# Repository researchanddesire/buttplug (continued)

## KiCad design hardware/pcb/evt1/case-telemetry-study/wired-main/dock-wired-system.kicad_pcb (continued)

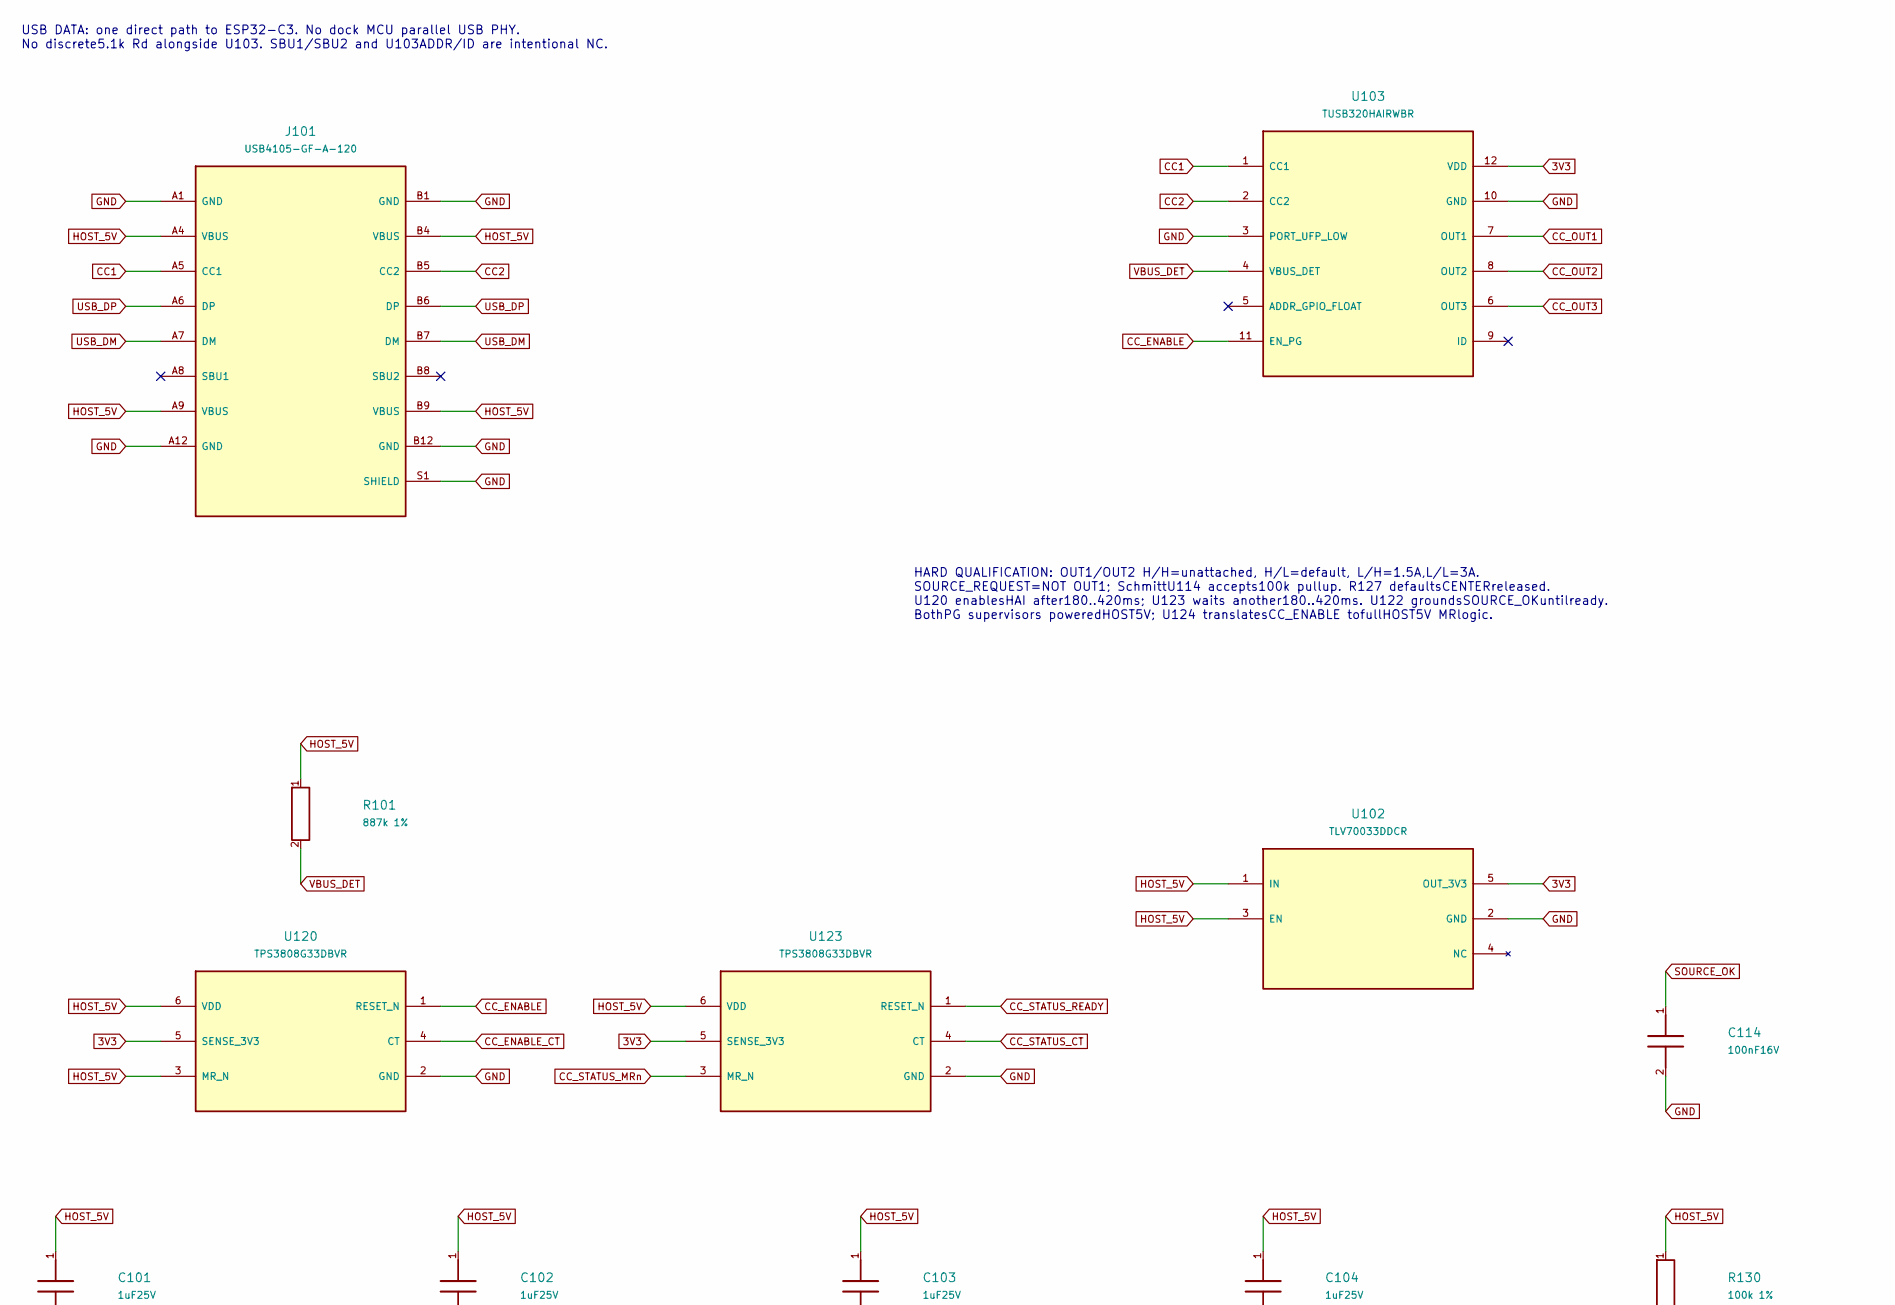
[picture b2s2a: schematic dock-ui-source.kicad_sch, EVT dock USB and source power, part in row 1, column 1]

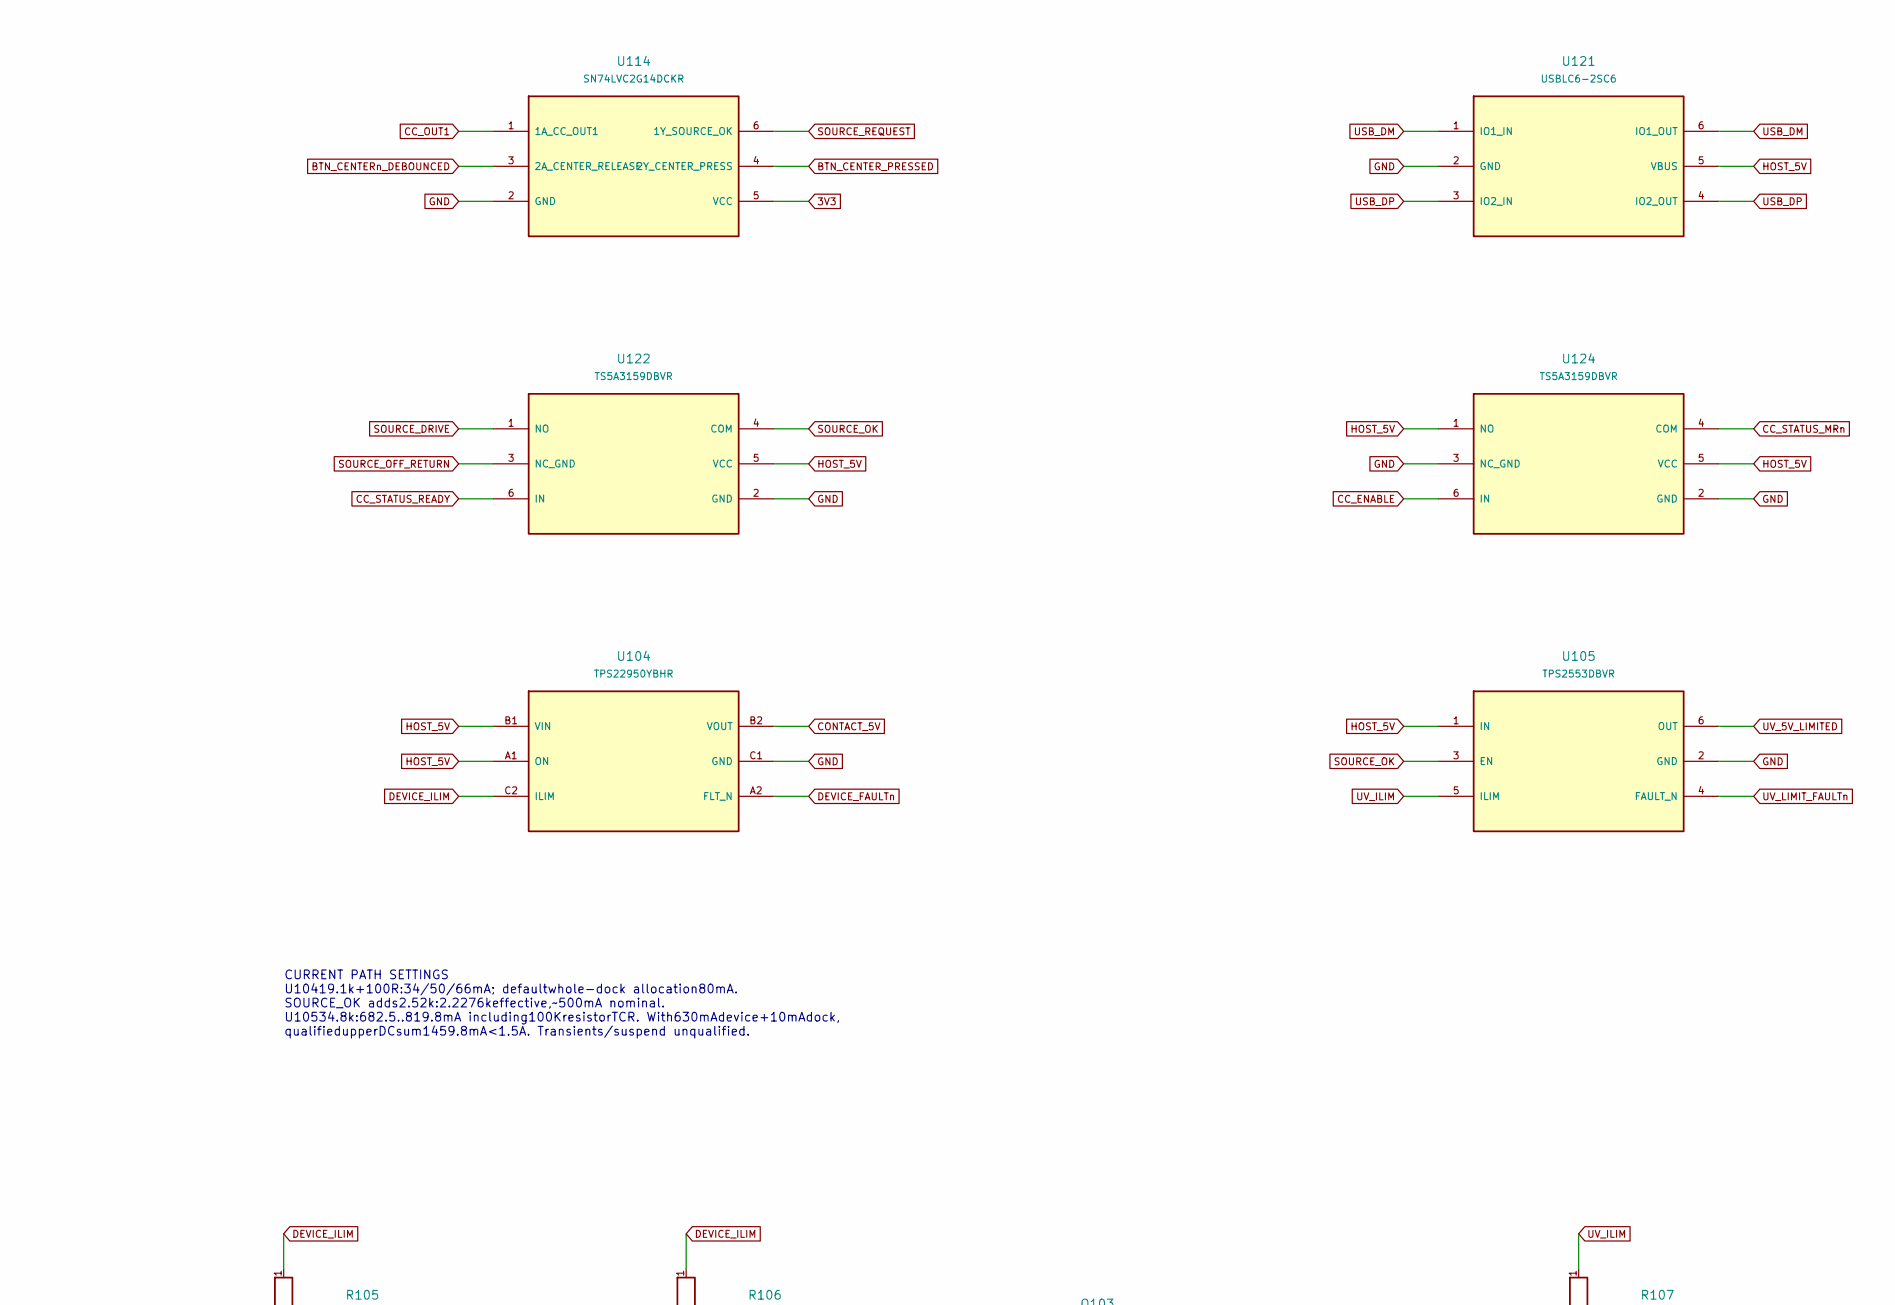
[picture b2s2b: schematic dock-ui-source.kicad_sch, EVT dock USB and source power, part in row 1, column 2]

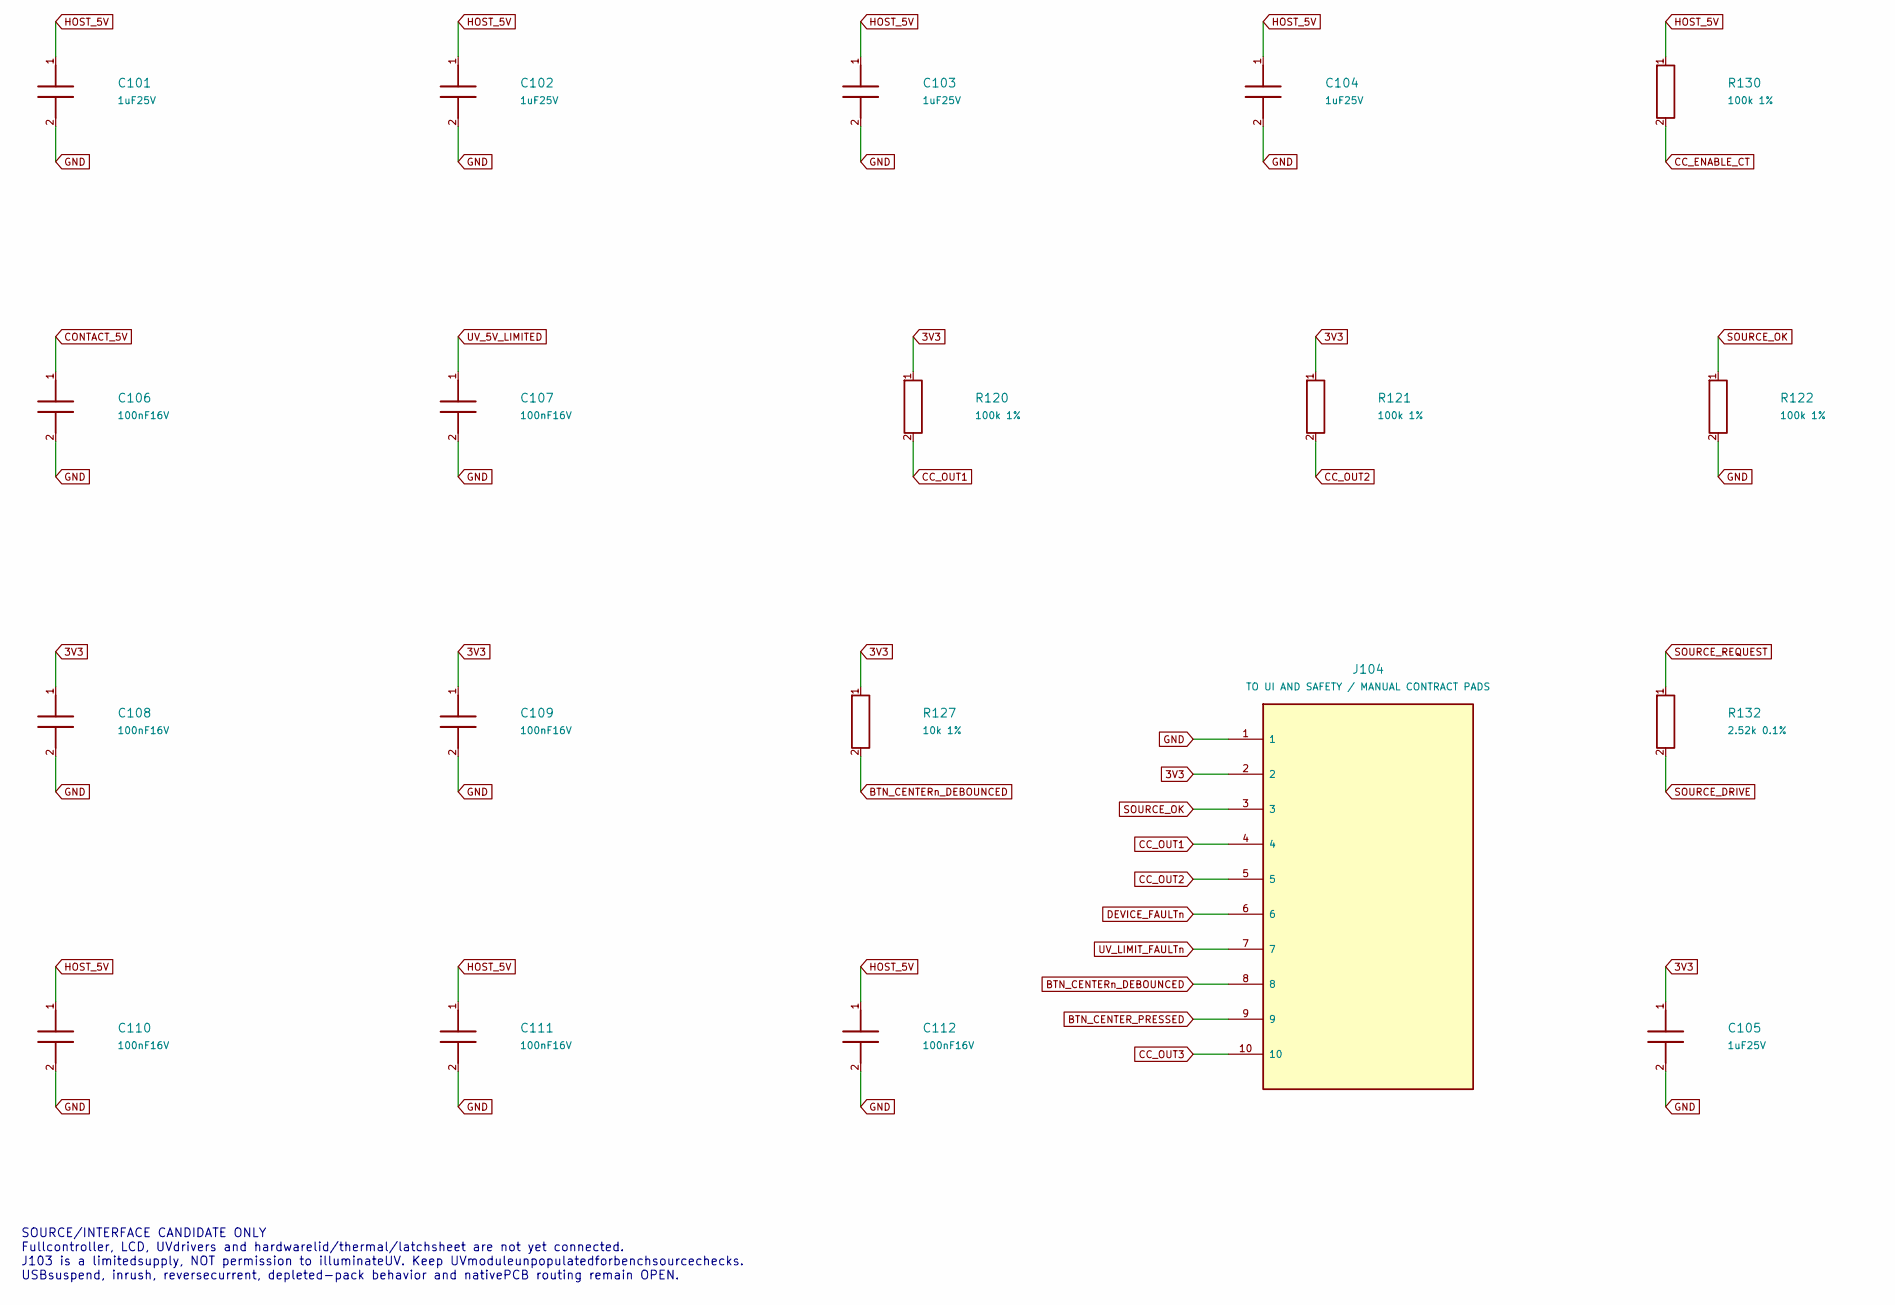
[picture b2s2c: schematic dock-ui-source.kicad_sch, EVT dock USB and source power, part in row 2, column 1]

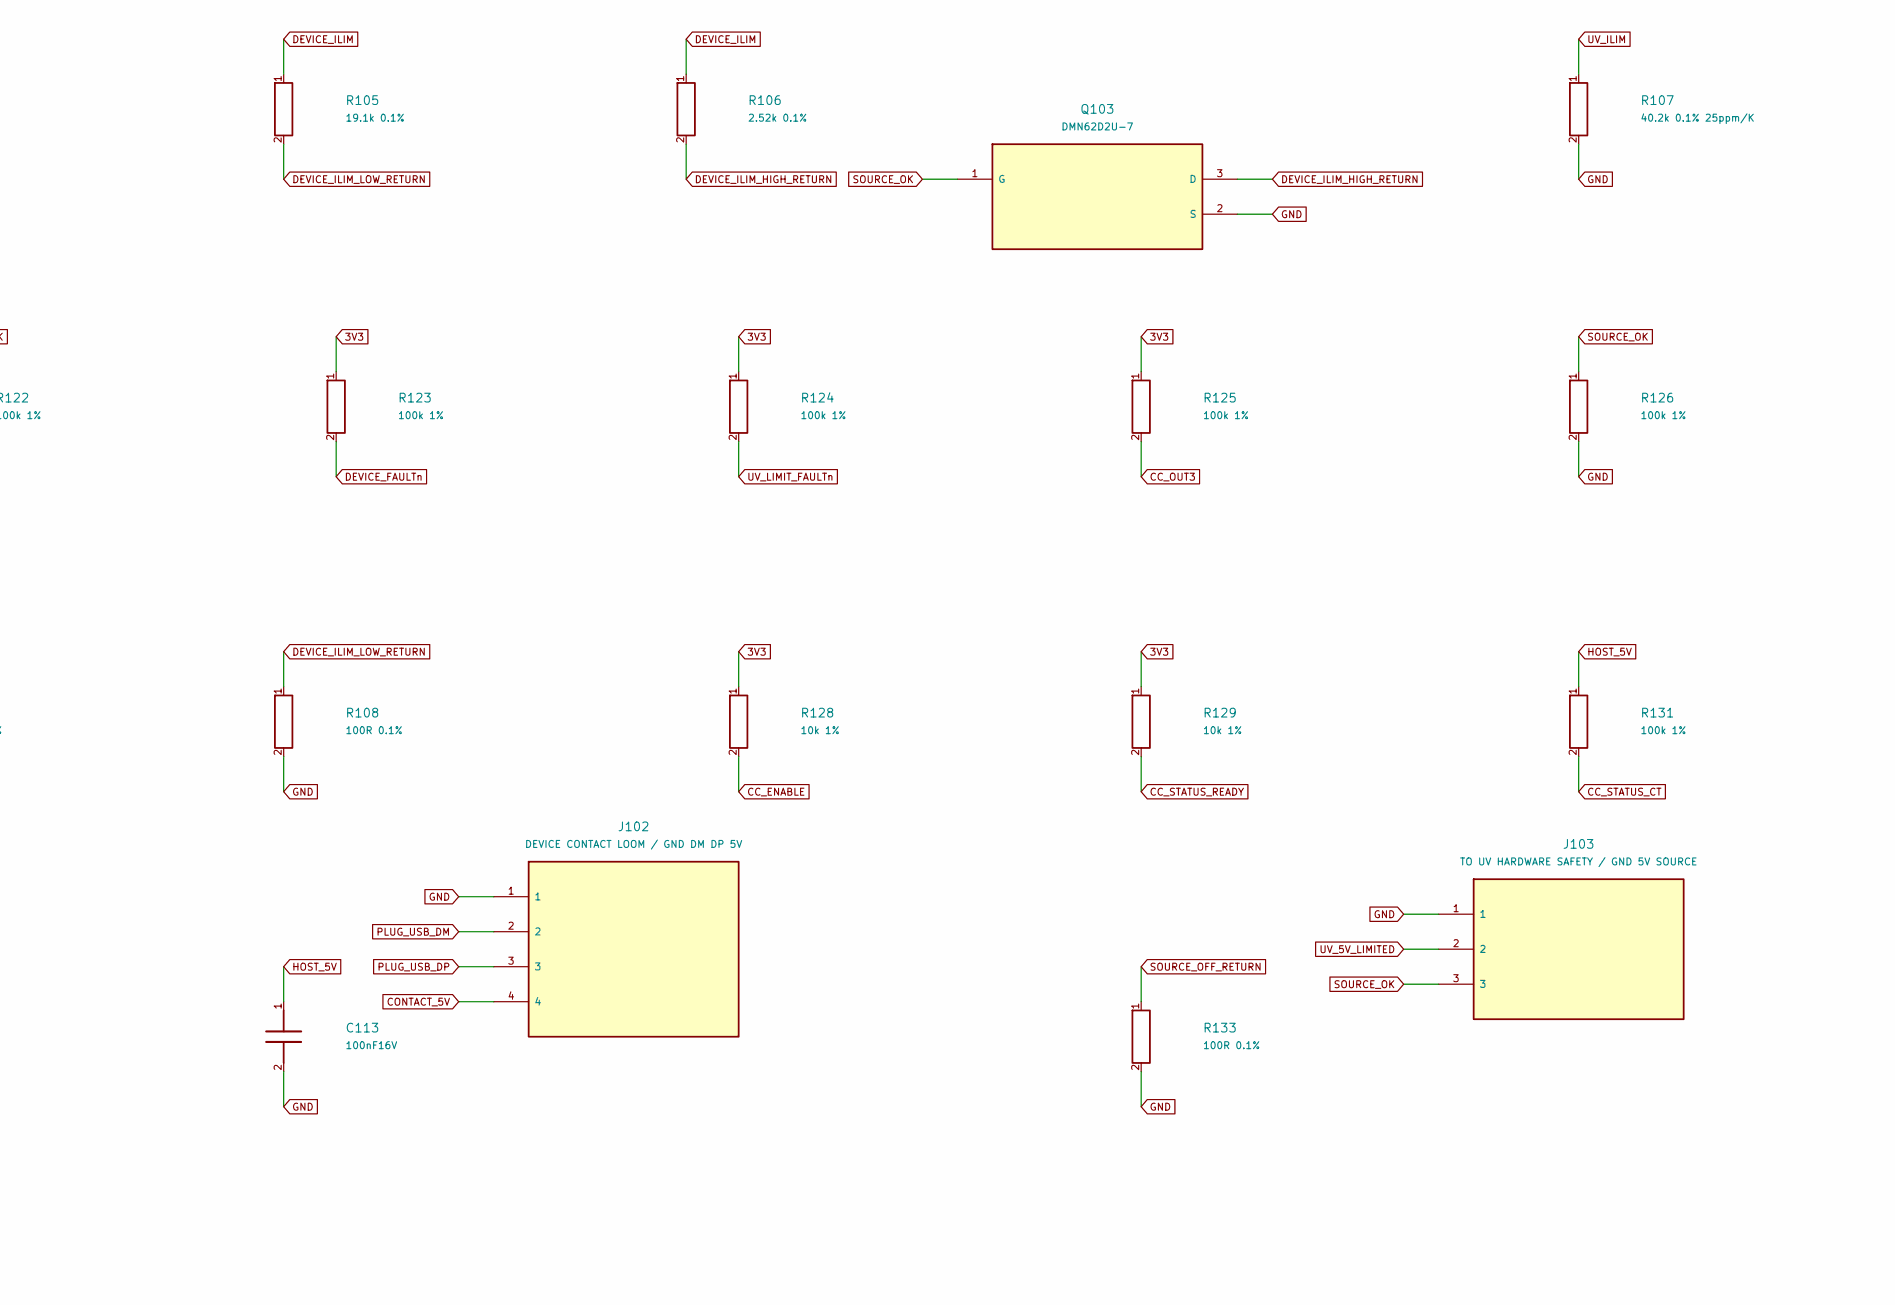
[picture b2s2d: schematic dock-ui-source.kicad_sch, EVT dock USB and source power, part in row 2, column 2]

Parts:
C101, C102, C103, C104, C105: 1uF25V; C_0603_1608Metric; MPN C1608X7R1E105K080AB
C106, C107, C108, C109, C110, C111, C112, C113, C114: 100nF16V; C_0402_1005Metric; MPN GRM155R71C104KA88D
J101: USB4105-GF-A-120; USB_C_Receptacle_GCT_USB4105-xx-A_16P_TopMnt_Horizontal; MPN USB4105-GF-A-120
J102: DEVICE CONTACT LOOM / GND DM DP 5V; Contact_Loom_4Land; MPN DEVICE CONTACT LOOM / GND DM DP 5V
J103: TO UV HARDWARE SAFETY / GND 5V SOURCE; Control_Loom_3Land; MPN TO UV HARDWARE SAFETY / GND 5V SOURCE
J104: TO UI AND SAFETY / MANUAL CONTRACT PADS; Control_Loom_10Land; MPN TO UI AND SAFETY / MANUAL CONTRACT PADS
Q103: DMN62D2U-7; SOT-23; MPN DMN62D2U-7
R101: 887k 1%; R_0603_1608Metric; MPN RC0603FR-07887KL
R105: 19.1k 0.1%; R_0603_1608Metric; MPN RT0603BRD0719K1L
R106, R132: 2.52k 0.1%; R_0603_1608Metric; MPN RT0603BRD072K52L
R107: 40.2k 0.1% 25ppm/K; R_0603_1608Metric; MPN RT0603BRD0740K2L
R108, R133: 100R 0.1%; R_0603_1608Metric; MPN RT0603BRD07100RL
R120, R121, R122, R123, R124, R125, R126, R130, R131: 100k 1%; R_0603_1608Metric; MPN RC0603FR-07100KL
R127, R128, R129: 10k 1%; R_0603_1608Metric; MPN RC0603FR-0710KL
U102: TLV70033DDCR; TSOT-23-5; MPN TLV70033DDCR
U103: TUSB320HAIRWBR; Texas_X2QFN-12_1.6x1.6mm_P0.4mm; MPN TUSB320HAIRWBR
U104: TPS22950YBHR; Texas_YBH0006-C02_DSBGA-6_1.106x0.706mm_P0.4mm; MPN TPS22950YBHR
U105: TPS2553DBVR; SOT-23-6; MPN TPS2553DBVR
U114: SN74LVC2G14DCKR; SOT-363_SC-70-6; MPN SN74LVC2G14DCKR
U120, U123: TPS3808G33DBVR; SOT-23-6; MPN TPS3808G33DBVR
U121: USBLC6-2SC6; SOT-23-6; MPN USBLC6-2SC6
U122, U124: TS5A3159DBVR; SOT-23-6; MPN TS5A3159DBVR

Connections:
3V3: C105.1, C108.1, C109.1, J104.2, R120.1, R121.1, R123.1, R124.1, R125.1, R127.1, R128.1, R129.1, U102.5 (OUT_3V3), U103.12 (VDD), U114.5 (VCC), U120.5 (SENSE_3V3), U123.5 (SENSE_3V3); also elsewhere on the board
BTN_CENTER_PRESSED: J104.9, U114.4 (2Y_CENTER_PRESS); also elsewhere on the board
BTN_CENTERn_DEBOUNCED: J104.8, R127.2, U114.3 (2A_CENTER_RELEASE); also elsewhere on the board
CC1: J101.A5 (CC1), U103.1 (CC1)
CC2: J101.B5 (CC2), U103.2 (CC2)
CC_ENABLE: R128.2, U103.11 (EN_PG), U120.1 (RESET_N), U124.6 (IN); also elsewhere on the board
CC_ENABLE_CT: R130.2, U120.4 (CT)
CC_OUT1: J104.4, R120.2, U103.7 (OUT1), U114.1 (1A_CC_OUT1); also elsewhere on the board
CC_OUT2: J104.5, R121.2, U103.8 (OUT2); also elsewhere on the board
CC_OUT3: J104.10, R125.2, U103.6 (OUT3)
CC_STATUS_CT: R131.2, U123.4 (CT)
CC_STATUS_MRn: U123.3 (MR_N), U124.4 (COM)
CC_STATUS_READY: R129.2, U122.6 (IN), U123.1 (RESET_N)
CONTACT_5V: C106.1, J102.4, U104.B2 (VOUT); also elsewhere on the board
DEVICE_FAULTn: J104.6, R123.2, U104.A2 (FLT_N); also elsewhere on the board
DEVICE_ILIM: R105.1, R106.1, U104.C2 (ILIM)
DEVICE_ILIM_HIGH_RETURN: Q103.3 (D), R106.2
DEVICE_ILIM_LOW_RETURN: R105.2, R108.1
GND: C101.2, C102.2, C103.2, C104.2, C105.2, C106.2, C107.2, C108.2, C109.2, C110.2, C111.2, C112.2, C113.2, C114.2, J101.A1 (GND), J101.A12 (GND), J101.B1 (GND), J101.B12 (GND), J101.S1 (SHIELD), J102.1, J103.1, J104.1, Q103.2 (S), R107.2, R108.2, R122.2, R126.2, R133.2, U102.2 (GND), U103.3 (PORT_UFP_LOW), U103.10 (GND), U104.C1 (GND), U105.2 (GND), U114.2 (GND), U120.2 (GND), U121.2 (GND), U122.2 (GND), U123.2 (GND), U124.2 (GND), U124.3 (NC_GND); also elsewhere on the board
HOST_5V: C101.1, C102.1, C103.1, C104.1, C110.1, C111.1, C112.1, C113.1, J101.A4 (VBUS), J101.A9 (VBUS), J101.B4 (VBUS), J101.B9 (VBUS), R101.1, R130.1, R131.1, U102.1 (IN), U102.3 (EN), U104.A1 (ON), U104.B1 (VIN), U105.1 (IN), U120.3 (MR_N), U120.6 (VDD), U121.5 (VBUS), U122.5 (VCC), U123.6 (VDD), U124.1 (NO), U124.5 (VCC); also elsewhere on the board
PLUG_USB_DM: J102.2; also elsewhere on the board
PLUG_USB_DP: J102.3; also elsewhere on the board
SOURCE_DRIVE: R132.2, U122.1 (NO)
SOURCE_OFF_RETURN: R133.1, U122.3 (NC_GND)
SOURCE_OK: C114.1, J103.3, J104.3, Q103.1 (G), R122.1, R126.1, U105.3 (EN), U122.4 (COM); also elsewhere on the board
SOURCE_REQUEST: R132.1, U114.6 (1Y_SOURCE_OK)
USB_DM: J101.A7 (DM), J101.B7 (DM), U121.1 (IO1_IN), U121.6 (IO1_OUT); also elsewhere on the board
USB_DP: J101.A6 (DP), J101.B6 (DP), U121.3 (IO2_IN), U121.4 (IO2_OUT); also elsewhere on the board
UV_5V_LIMITED: C107.1, J103.2, U105.6 (OUT); also elsewhere on the board
UV_ILIM: R107.1, U105.5 (ILIM)
UV_LIMIT_FAULTn: J104.7, R124.2, U105.4 (FAULT_N); also elsewhere on the board
VBUS_DET: R101.2, U103.4 (VBUS_DET)

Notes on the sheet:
USB DATA: one direct path to ESP32-C3. No dock MCU parallel USB PHY. No discrete5.1k Rd alongside U103. SBU1/SBU2 and U103ADDR/ID are intentional NC.
HARD QUALIFICATION: OUT1/OUT2 H/H=unattached, H/L=default, L/H=1.5A,L/L=3A. SOURCE_REQUEST=NOT OUT1; SchmittU114 accepts100k pullup. R127 defaultsCENTERreleased. U120 enablesHAI after180..420ms; U123 waits another180..420ms. U122 groundsSOURCE_OKuntilready. BothPG supervisors poweredHOST5V; U124 tr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
CURRENT PATH SETTINGS U10419.1k+100R:34/50/66mA; defaultwhole-dock allocation80mA. SOURCE_OK adds2.52k:2.2276keffective,~500mA nominal. U10534.8k:682.5..819.8mA including100KresistorTCR. With630mAdevice+10mAdock, qualifiedupperDCsum1459.8mA<1.5A. Transients/suspend unqualified.
SOURCE/INTERFACE CANDIDATE ONLY Fullcontroller, LCD, UVdrivers and hardwarelid/thermal/latchsheet are not yet connected. J103 is a limitedsupply, NOT permission to illuminateUV. Keep UVmoduleunpopulatedforbenchsourcechecks. USBsuspend, inrush, reversecurrent, depleted-pack behavior and nativePCB ro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

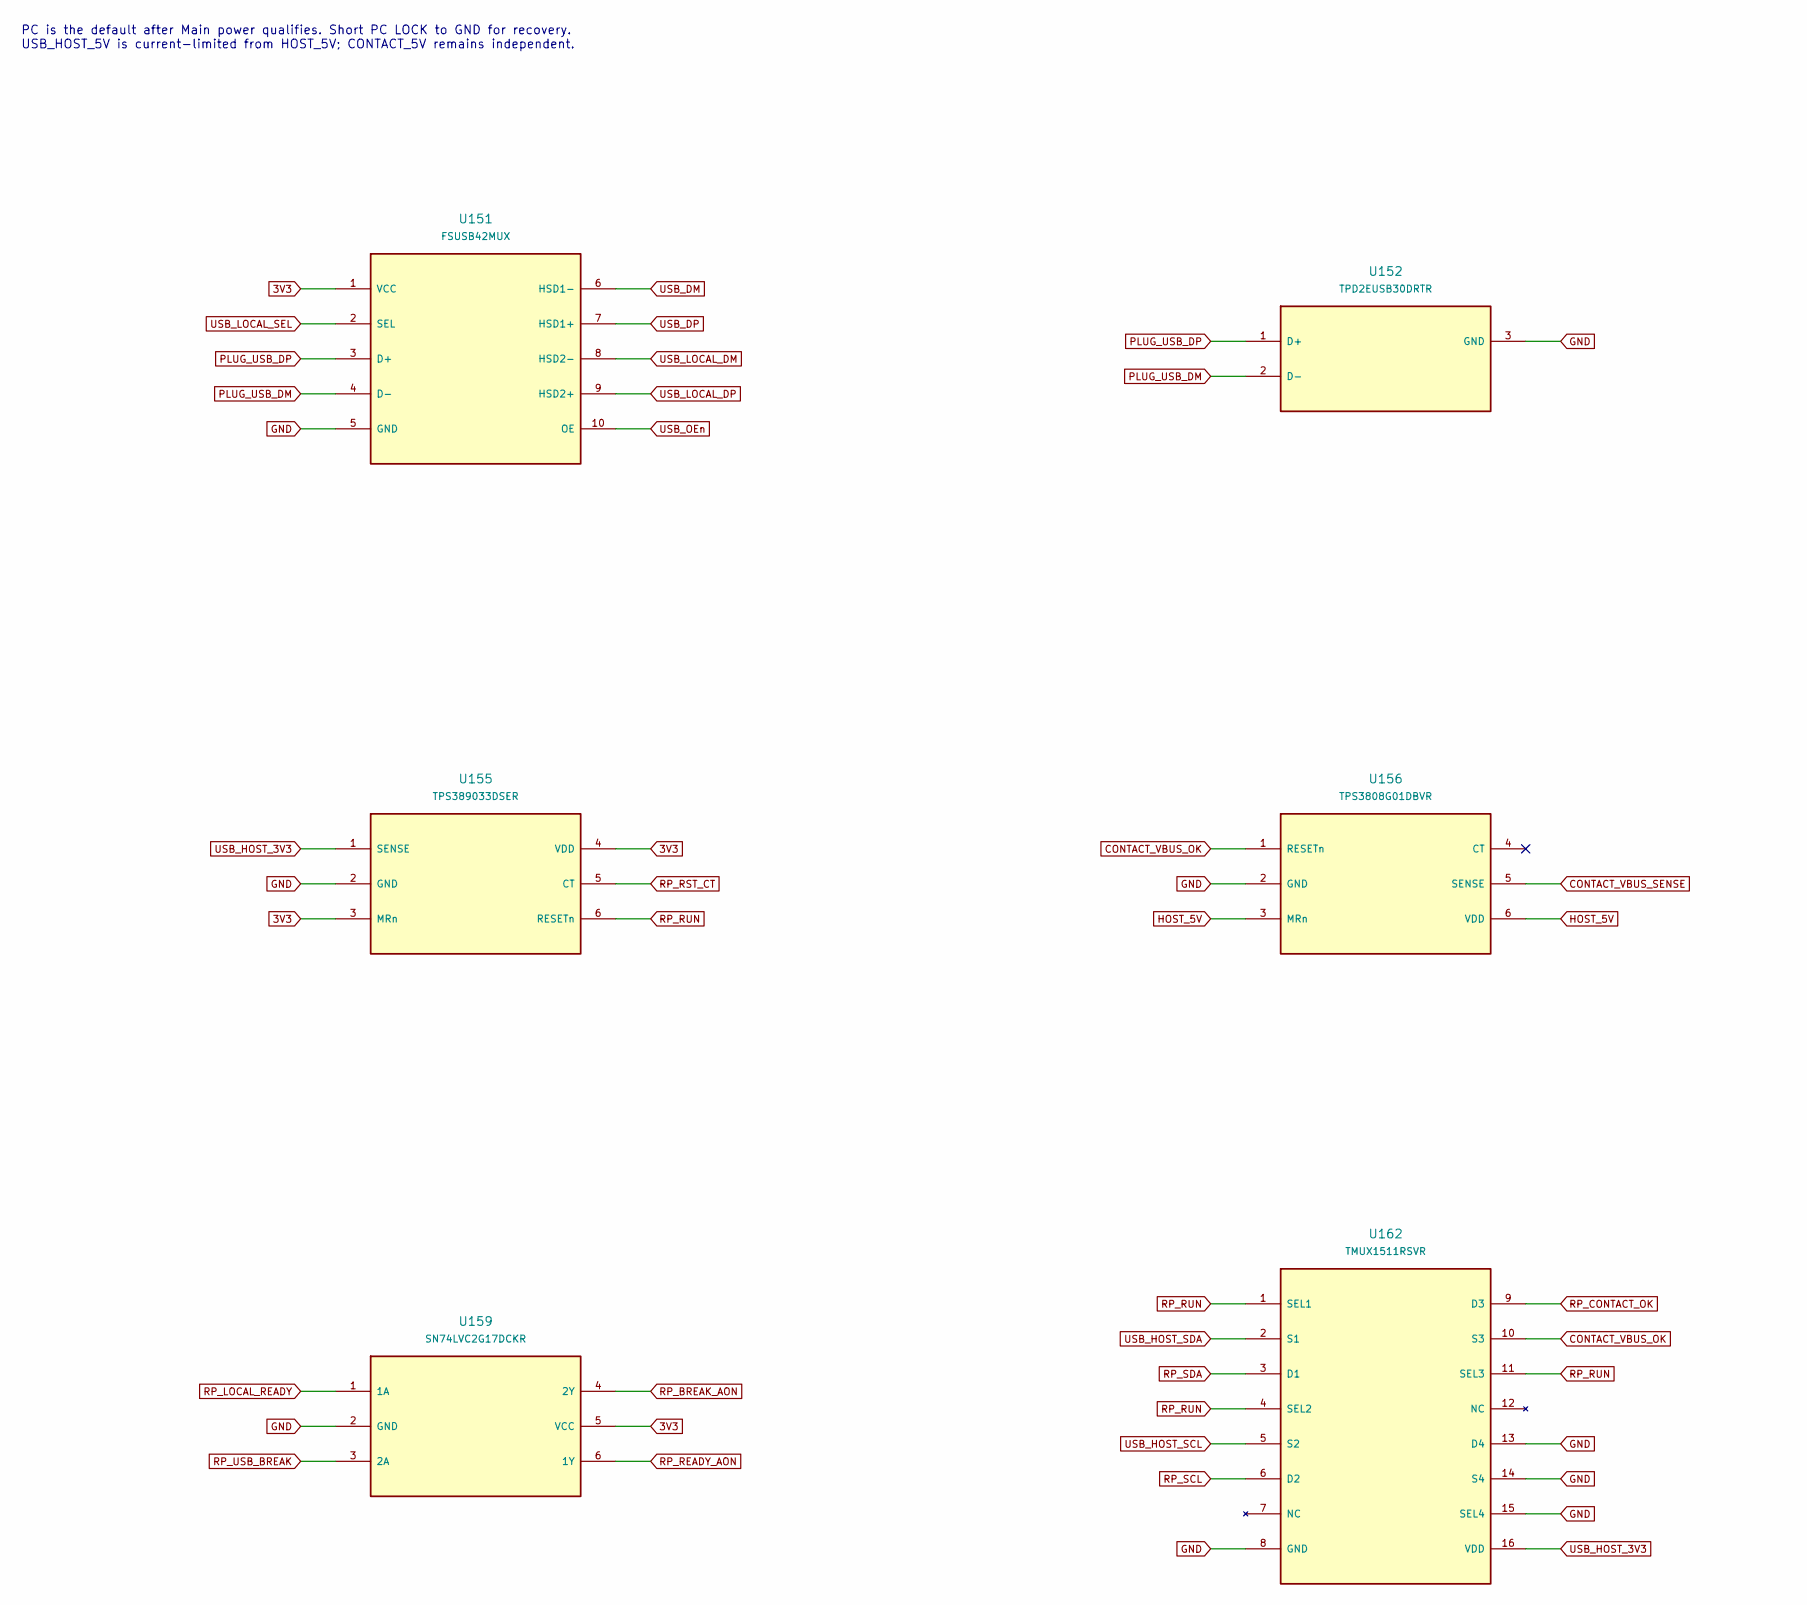
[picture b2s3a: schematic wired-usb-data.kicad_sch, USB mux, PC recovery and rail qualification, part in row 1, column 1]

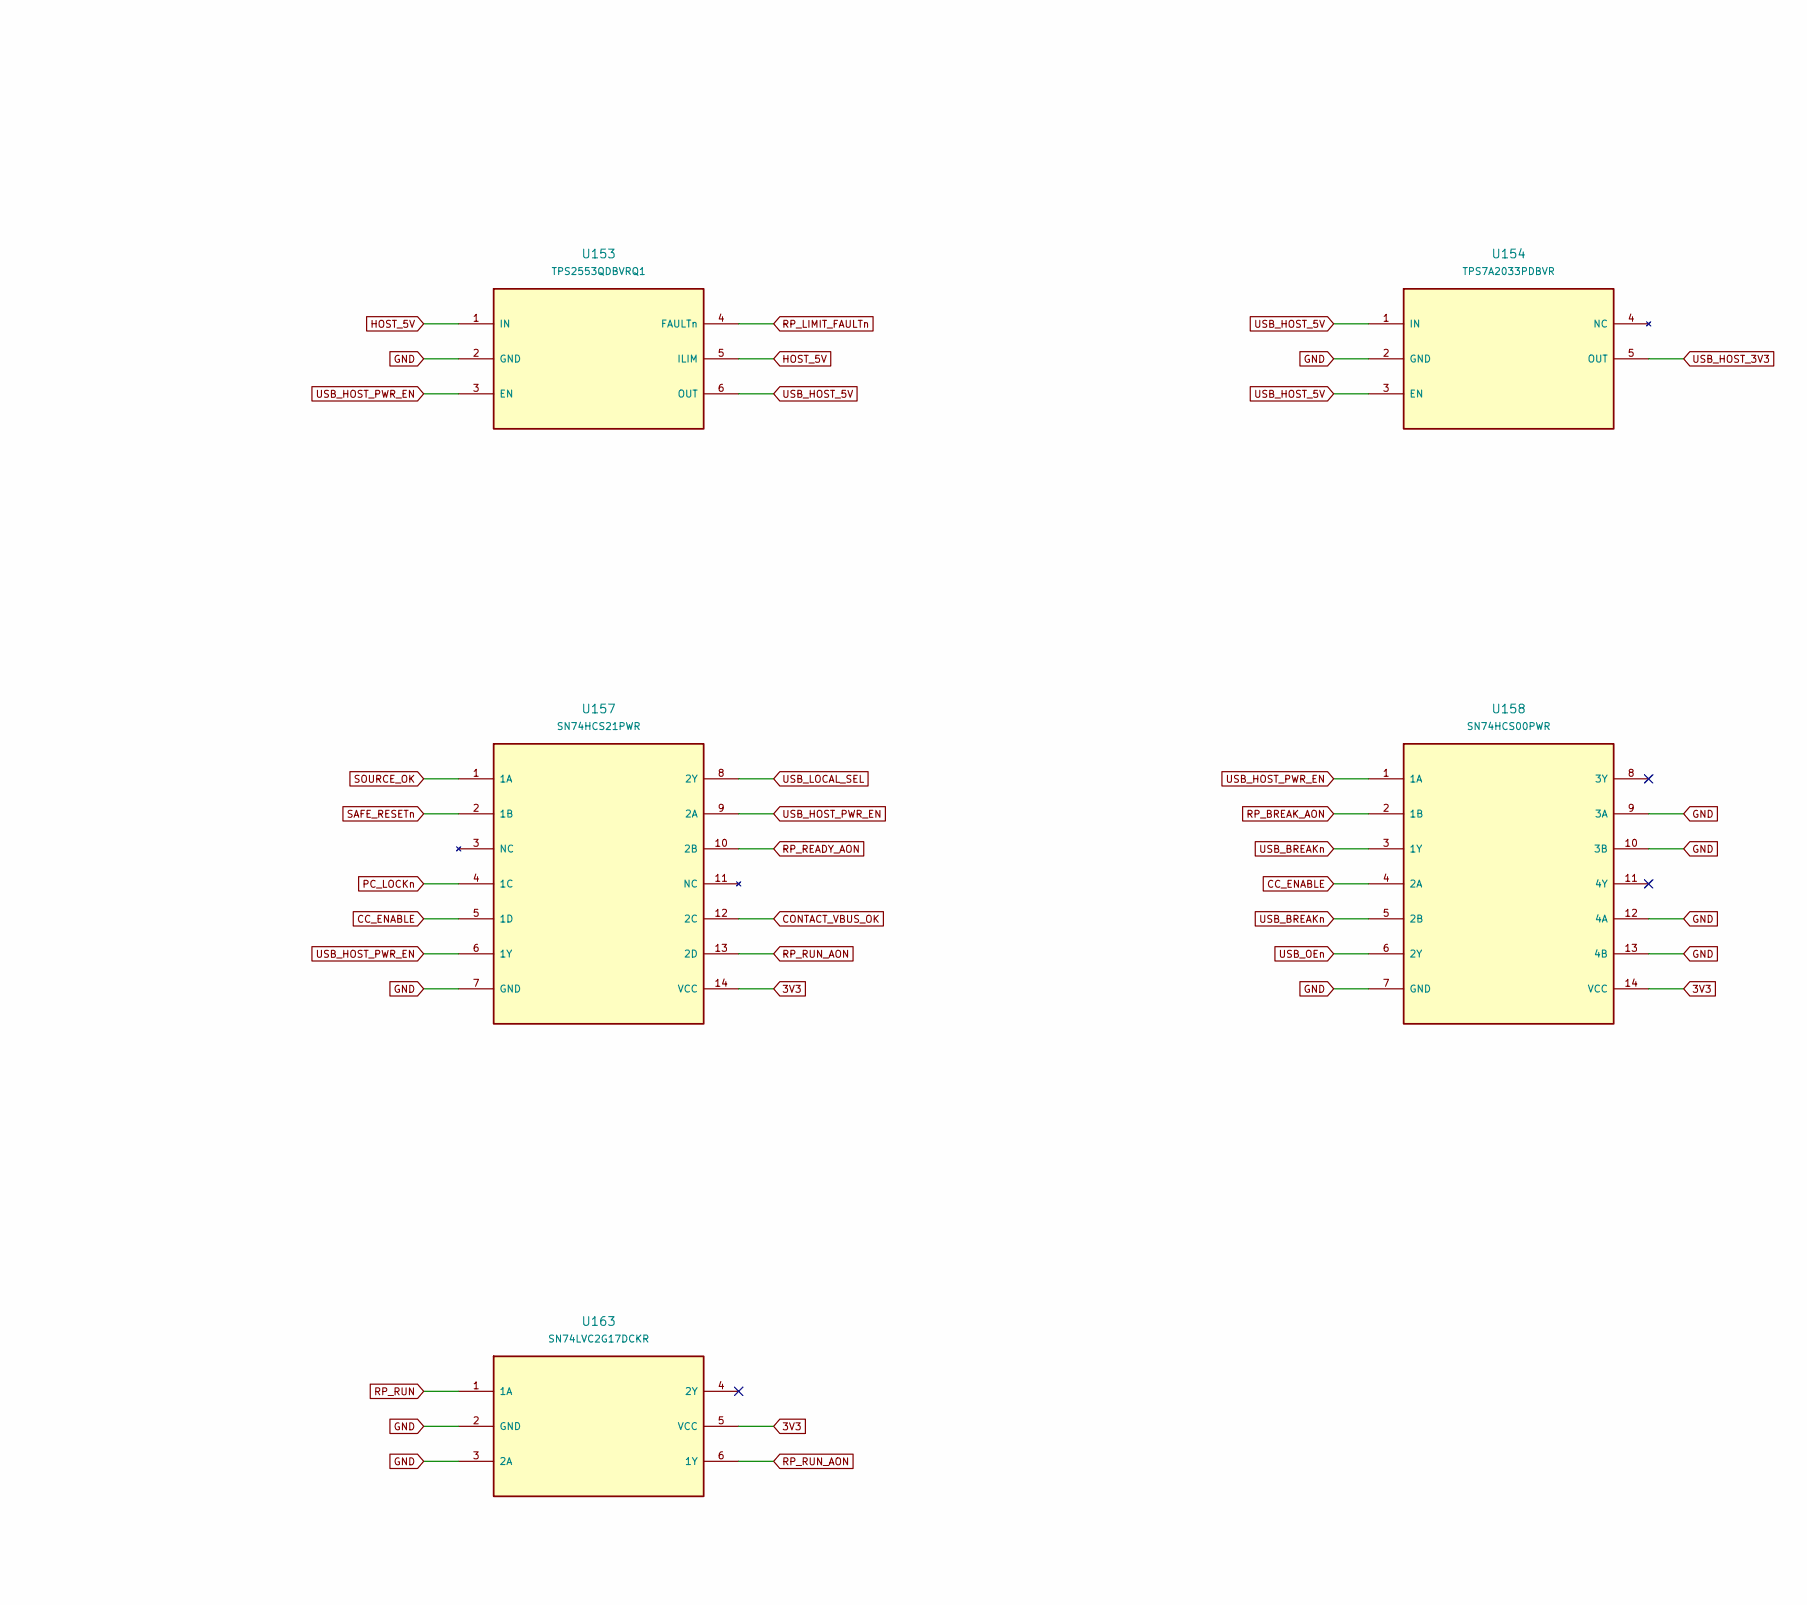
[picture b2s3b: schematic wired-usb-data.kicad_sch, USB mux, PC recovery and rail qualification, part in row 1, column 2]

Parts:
U151: FSUSB42MUX; Onsemi_846AP_MSOP10; MPN FSUSB42MUX
U152: TPD2EUSB30DRTR; Texas_DRT-3; MPN TPD2EUSB30DRTR
U153: TPS2553QDBVRQ1; SOT-23-6; MPN TPS2553QDBVRQ1
U154: TPS7A2033PDBVR; SOT-23-5; MPN TPS7A2033PDBVR
U155: TPS389033DSER; TI_DSE0006A; MPN TPS389033DSER
U156: TPS3808G01DBVR; SOT-23-6; MPN TPS3808G01DBVR
U157: SN74HCS21PWR; TSSOP-14_4.4x5mm_P0.65mm; MPN SN74HCS21PWR
U158: SN74HCS00PWR; TSSOP-14_4.4x5mm_P0.65mm; MPN SN74HCS00PWR
U159, U163: SN74LVC2G17DCKR; SOT-363_SC-70-6; MPN SN74LVC2G17DCKR
U162: TMUX1511RSVR; TI_RSV0016A; MPN TMUX1511RSVR

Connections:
3V3: U151.1 (VCC), U155.3 (MRn), U155.4 (VDD), U157.14 (VCC), U158.14 (VCC), U159.5 (VCC), U163.5 (VCC); also elsewhere on the board
CC_ENABLE: U157.5 (1D), U158.4 (2A); also elsewhere on the board
CONTACT_VBUS_OK: U156.1 (RESETn), U157.12 (2C), U162.10 (S3); also elsewhere on the board
CONTACT_VBUS_SENSE: U156.5 (SENSE); also elsewhere on the board
GND: U151.5 (GND), U152.3 (GND), U153.2 (GND), U154.2 (GND), U155.2 (GND), U156.2 (GND), U157.7 (GND), U158.7 (GND), U158.9 (3A), U158.10 (3B), U158.12 (4A), U158.13 (4B), U159.2 (GND), U162.8 (GND), U162.13 (D4), U162.14 (S4), U162.15 (SEL4), U163.2 (GND), U163.3 (2A); also elsewhere on the board
HOST_5V: U153.1 (IN), U153.5 (ILIM), U156.3 (MRn), U156.6 (VDD); also elsewhere on the board
PC_LOCKn: U157.4 (1C); also elsewhere on the board
PLUG_USB_DM: U151.4 (D−), U152.2 (D−); also elsewhere on the board
PLUG_USB_DP: U151.3 (D+), U152.1 (D+); also elsewhere on the board
RP_BREAK_AON: U158.2 (1B), U159.4 (2Y)
RP_CONTACT_OK: U162.9 (D3); also elsewhere on the board
RP_LIMIT_FAULTn: U153.4 (FAULTn); also elsewhere on the board
RP_LOCAL_READY: U159.1 (1A); also elsewhere on the board
RP_READY_AON: U157.10 (2B), U159.6 (1Y)
RP_RST_CT: U155.5 (CT); also elsewhere on the board
RP_RUN: U155.6 (RESETn), U162.1 (SEL1), U162.4 (SEL2), U162.11 (SEL3), U163.1 (1A); also elsewhere on the board
RP_RUN_AON: U157.13 (2D), U163.6 (1Y)
RP_SCL: U162.6 (D2); also elsewhere on the board
RP_SDA: U162.3 (D1); also elsewhere on the board
RP_USB_BREAK: U159.3 (2A); also elsewhere on the board
SAFE_RESETn: U157.2 (1B); also elsewhere on the board
SOURCE_OK: U157.1 (1A); also elsewhere on the board
USB_BREAKn: U158.3 (1Y), U158.5 (2B)
USB_DM: U151.6 (HSD1−); also elsewhere on the board
USB_DP: U151.7 (HSD1+); also elsewhere on the board
USB_HOST_3V3: U154.5 (OUT), U155.1 (SENSE), U162.16 (VDD); also elsewhere on the board
USB_HOST_5V: U153.6 (OUT), U154.1 (IN), U154.3 (EN); also elsewhere on the board
USB_HOST_PWR_EN: U153.3 (EN), U157.6 (1Y), U157.9 (2A), U158.1 (1A); also elsewhere on the board
USB_HOST_SCL: U162.5 (S2); also elsewhere on the board
USB_HOST_SDA: U162.2 (S1); also elsewhere on the board
USB_LOCAL_DM: U151.8 (HSD2−); also elsewhere on the board
USB_LOCAL_DP: U151.9 (HSD2+); also elsewhere on the board
USB_LOCAL_SEL: U151.2 (SEL), U157.8 (2Y); also elsewhere on the board
USB_OEn: U151.10 (OE), U158.6 (2Y); also elsewhere on the board

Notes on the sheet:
PC is the default after Main power qualifies. Short PC LOCK to GND for recovery. USB_HOST_5V is current-limited from HOST_5V; CONTACT_5V remains independent.
